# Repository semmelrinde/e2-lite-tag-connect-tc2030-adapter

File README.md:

# Renesas E2 emulator Lite → Tag-Connect TC2030 adapter (hand-solder, open hardware)

A small, hand-solderable KiCad adapter board that connects a **Renesas E2 emulator Lite** (20-pin 1.27 mm debug connector, RA family / SWD) to a **Tag-Connect TC2030-IDC** cable, so you can program and debug Renesas RA MCUs through a TC2030 footprint (for example RA8, RA6, RA4) without a header on your board.

| Top | Bottom |
|---|---|
|  |  |

*Renders from KiCad. The 3D model of J1 is a plain pin header; the real part is a shrouded box header.*

**Status (November 2026):** design finished and checked (ERC 0, DRC 0 errors / 0 warnings / 0 unconnected / schematic parity 0, two independent reviews of every connection). Not built yet. Reports from builders are welcome via Issues.

Deutsch: [Kurzfassung unten](#deutsch).

---

## What it does

```
E2 Lite ── 20-pin 1.27 mm ribbon cable ── J1 [adapter] J2 ── TC2030-IDC cable ── TC2030 footprint on your board
```

| J1 (E2 Lite, 20-pin) | Signal | On the adapter | J2 / TC2030 | Target |
|---|---|---|---|---|
| 1 | VCC (target voltage reference) | U1 ideal diode (target → emulator) | 1 | VTref |
| 2 | SWDIO | R1 100 Ω | 2 | SWDIO |
| 4 | SWCLK | R2 100 Ω | 4 | SWCLK |
| 10 | RES# | R3 100 Ω | 3 | nRESET |
| 3, 5, 9 (UCON), 15, 17, 19 | GND | direct | 5 | GND |
| 6, 7, 8, 11–14, 16, 18, 20 | – | not connected | 6 (SWO) not connected | – |

- The J1 pinout follows the Renesas document *E2 Emulator, E2 Emulator Lite Additional Document for User's Manual (Notes on Connection of RA Devices)*, R20UT4686, Table 2.3 (SWD). **Pin 9 (UCON) must be tied to GND**, otherwise the E2 Lite does not detect the target.
- The J2 pinout is the common TC2030 SWD layout: 1 VTref, 2 SWDIO, 3 nRESET, 4 SWCLK, 5 GND, 6 SWO. With the TC2030-IDC cable, pin n of the footprint goes to pin n of the 2×3 IDC plug.
- The E2 Lite has no SWO trace input (pin 6 is a UART TxD on the E2 Lite), so SWO stays open.

## Protection (and its limits)

- **U1 LM66100 ideal diode** (CE tied to VOUT, ST to GND, as in TI's "always-on reverse current blocking" application). The E2 Lite powers its I/O buffers from the VCC pin (about 20 mA). Your board's supply reaches the emulator through U1 with only a few mV drop.
- **What U1 blocks:** target board **off** and the emulator set to supply 3.3 V by mistake. U1 blocks, so 3.3 V does not reach your target's rail.
- **What U1 does not block reliably:** target board **on** and the emulator supplying 3.3 V at the same time. U1 only switches off at several hundred mA reverse current; the E2 Lite supplies at most 200 mA.
- **R1–R3 (100 Ω)** damp the cable and limit the current if 3.3 V levels ever reach a 1.8 V target. That limits damage, it does not prevent it.
- **Always set "Power Target From The Emulator" to No** in e² studio / Renesas Flash Programmer when the target has its own supply. The bottom silkscreen says so as well.
- The E2 Lite works from 1.8 V to 5.5 V target voltage. The adapter costs a few mV, so a target running at exactly 1.8 V is right at the lower limit.

## Bill of materials

| Ref | Qty | Part | Notes |
|---|---|---|---|
| J1 | 1 | 2×10 box header, 1.27 mm pitch, straight, through-hole, e.g. Samtec SHF-110-01-L-D-TH or a generic "DC3-20P 1.27 mm" | notch towards the board edge (odd-pin side), as on the silkscreen |
| J2 | 1 | 2×3 box header, 2.54 mm pitch, straight, through-hole, e.g. Würth 61200621621 or a generic "DC3-6P" | notch towards the middle of the board (odd-pin side), as on the silkscreen |
| U1 | 1 | TI LM66100DCKR (or the automotive LM66100QDCKRQ1, same pinout), SC-70-6 | footprint has extended pads for hand soldering |
| R1, R2, R3 | 3 | 100 Ω, 0603 | |
| C1, C2 | 2 | 100 nF, 0603, X7R | |
| C3 | 1 | 1 µF, 0603 | 470 nF … 2.2 µF also fine |

You also need:
- a **20-pin 1.27 mm IDC ribbon cable** (both plugs in the same orientation, pin 1 to pin 1). The Renesas cable RTE0T00020KCAC0000J fits for sure.
- a **Tag-Connect TC2030-IDC** (with legs) or **TC2030-IDC-NL** (no legs) cable from [Tag-Connect](https://www.tag-connect.com/product/tc2030-idc-6-pin-tag-connect-plug-of-nails-spring-pin-cable-with-legs).
- a **Renesas E2 emulator Lite** (RTE0T0002LKCE00000R), for example from DigiKey or Mouser.

### Where to get the small parts

**If you buy the E2 Lite from DigiKey anyway, get the small parts there too.** They add only a few francs, the order stays above the free-shipping threshold, and you get genuine parts. Prices and stock checked at DigiKey Switzerland on 4 November 2026 (without VAT, will change):

| Ref | Part number | Price | Notes |
|---|---|---|---|
| J1 | Samtec SHF-110-01-L-D-TH | CHF 2.25 | 19 mm long, about 0.4 mm longer than the outline on the board at the outer edge; harmless. Pins 0.41 mm square in 0.65 mm holes: a snug fit. |
| J2 | Würth 61200621621 | CHF 0.41 | |
| U1 | TI LM66100QDCKRQ1 (cut tape) | CHF 0.31 | LM66100DCKR was out of stock; the Q1 part is the automotive grade of the same chip |

#### AliExpress (checked November 2026)

Listings change, so every part also has a description and search words. The links are examples, not recommendations of a particular seller. Check the variant (pitch and pin count) before you pay.

| Part | Example listing | Choose this variant | Search words if the link is dead |
|---|---|---|---|
| J1 box header, 1.27 mm 2×10 | [item 1005006195593825](https://de.aliexpress.com/item/1005006195593825.html) | **1.27 mm, 20P**, straight (DIP) | `1.27mm box header 2x10 DC3 straight DIP` |
| J2 box header, 2.54 mm 2×3 | [item 1005007258589531](https://de.aliexpress.com/item/1005007258589531.html) (AliExpress Choice) or [item 1005006195593825](https://de.aliexpress.com/item/1005006195593825.html) | **6Pin** (10 pcs), straight (DIP) | `2.54mm box header 2x3 6P straight DC3` |
| U1 LM66100DCKR | [item 1005013241477993](https://de.aliexpress.com/item/1005013241477993.html) | 10 pcs, SC-70-6 | `LM66100DCKR SC70-6` |
| 20-pin 1.27 mm cable (alternative to the Renesas cable) | [item 1005006165132728](https://de.aliexpress.com/item/1005006165132728.html) | **pitch 1.27 mm**, 20P, same direction | `1.27mm IDC flat cable 20 pin 2x10 same direction` |
| 0603 resistor and capacitor kits | any 0603 kit with 100 Ω, 100 nF and 1 µF | | `0603 resistor kit`, `0603 capacitor kit 1pF-10uF` |

Shipping tip: on AliExpress every seller charges its own shipping, often more than the part itself. Choice items ship free once the Choice part of your order reaches the threshold (CHF 9 in Switzerland, November 2026).

Watch out: many "1.27 mm" ribbon cables have 2.54 mm plugs (the ribbon wires have a 1.27 mm pitch). For the E2 Lite you need **plugs with 1.27 mm pin pitch** (ribbon wire pitch 0.635 mm).

Pictures of the real parts: we do not copy seller photos (they belong to the sellers). The renders above show the footprints. Photos of an assembled board will be added once one is built.

## Ordering the PCB (JLCPCB or any other fab)

- Gerber files: [`fabrication/E2Lite_TC2030_Adapter_V1_gerbers.zip`](fabrication/E2Lite_TC2030_Adapter_V1_gerbers.zip)
- 2 layers, 26 × 19.5 mm, 1.6 mm FR-4, 1 oz copper, any colour, HASL (lead-free) or ENIG, tented vias, standard via size 0.3 mm (0.6 mm pad). No special options needed.

### Save money: add it to a PCB order you already have

If you work with Tag-Connect, you almost certainly have your own PCB in production anyway. Add the adapter as an extra design to that order (at JLCPCB: "Add new item" on the running order, or put both in the same cart). Everything then ships in one parcel.

Example from a JLCPCB quote on 4 November 2026 (5 pcs, shipping to Switzerland, prices in EUR, will change):

| | Board (5 pcs) | Shipping | Total |
|---|---|---|---|
| Ordered on its own | €3.66 (green HASL) … €4.64 (black, lead-free HASL) | €20.92 (DHL Express, 0.14 kg) | **€24.58 … €25.56** |
| Added to an order that ships anyway | €3.66 … €4.64 | about €0 (adds roughly 10 g) | **€3.66 … €4.64** |
| **You save** | | | **about €21 (≈ 82–85 %)** |

Shipping cost depends on your country, the carrier and the weight of the whole parcel. With JLCPCB the combined order only ships when every item in it is finished.

## Assembly (hand soldering)

1. **U1 first:** a little solder paste or flux, pin 1 (dot) at the silkscreen triangle. The pads are extended for a soldering iron.
2. **C1–C3, R1–R3** (0603, large pads).
3. **J1:** insert from the top, **notch on the outer edge (odd-pin side)** as on the silkscreen. The pins are 1.27 mm apart: use a fine tip and remove bridges with wick.
4. **J2:** notch towards the middle of the board, as on the silkscreen.
5. If U1 does not work (for example a bad part): remove it and bridge **pad 1 to pad 6** (same row, about 2 mm apart). VCC is then connected directly, as in Renesas' reference circuit, without the reverse-current protection.

## Check before first use (adapter alone, no target)

| From J1 | To J2 | Expected |
|---|---|---|
| 2 | 2 | ≈ 100 Ω |
| 4 | 4 | ≈ 100 Ω |
| 10 | 3 | ≈ 100 Ω |
| 3, 5, 9, 15, 17, 19 | 5 | 0 Ω |
| 1 | 1 | no short; diode test + at J2.1, − at J1.1: about 0.4–0.7 V (U1 body diode, estimate), reverse open |
| 1 vs 3 | 1 vs 5 | no short to GND |
| 6, 7, 8, 11–14, 16, 18, 20 | – | open |

Check the ribbon cable too: pin 1 must reach pin 1 at both ends (red wire).

### Power-up order (from the Renesas user manual)

1. Target off.
2. Connect adapter and cables.
3. Plug the E2 Lite into USB.
4. Start the debugger or flash tool, set "Power Target From The Emulator: No".
5. Switch the target on.
6. Connect in the software.

Reverse order when you finish. Do not unplug the E2 Lite's USB cable while the target is powered (Renesas warns about leakage currents).

## Files

```
hardware/      KiCad 10 project (schematic, PCB, footprints, 3D models from the KiCad library)
hardware/gen/  Python scripts that generate the schematic and the PCB (optional; macOS KiCad paths)
fabrication/   Gerber + drill files (zip)
images/        3D renders, schematic (PDF, SVG)
```

Custom footprints: `BoxHeader_2x10_P1.27mm_Vertical_DC3` (pins as KiCad `PinHeader_2x10_P1.27mm_Vertical`, drill 0.65 mm, assumed body 5.8 × 16.2 mm) and `SOT-363_SC-70-6_HandSolder` (KiCad pad positions, pads extended outwards).

## Related

- [ST-LINK V3 / ARM 20-pin → Tag-Connect TC2030 adapter](https://github.com/semmelrinde/stlink-v3-tag-connect-tc2030-adapter)

## Licence and disclaimer

- Hardware design, documentation and scripts: **CERN-OHL-P-2.0** ([LICENSE](LICENSE)). You may use, modify, make and sell it. The design comes without any warranty, see the licence.
- Footprints and 3D models taken from the KiCad libraries: CC-BY-SA 4.0 with the KiCad library exception, see [NOTICE.md](NOTICE.md).
- **Not affiliated with or endorsed by** Renesas Electronics, Tag-Connect LLC, Texas Instruments, Samtec, Würth Elektronik, DigiKey, AliExpress or any other manufacturer or shop. Product names and trademarks belong to their owners and are used only to describe compatibility. No manufacturer datasheets, manual text or seller photos are included; please get them from the original sources.
- You use this adapter at your own risk. Check pinouts against your own board and debugger before connecting anything.

---

## Deutsch

Kleiner Adapter zum Selberlöten: **Renesas E2 emulator Lite** (20-polig, 1,27 mm) auf **Tag-Connect TC2030-IDC**. Damit programmierst und debuggst du Renesas-RA-Mikrocontroller über ein TC2030-Pad.

- **Belegung:** wie in der Tabelle oben. Pin 9 (UCON) liegt auf Masse.
- **Schutz:** Die Idealdiode LM66100 schützt nur bei ausgeschaltetem Zielboard vor den 3,3 V des Emulators. Darum im Programm immer „Power Target From The Emulator: No“ einstellen.
- **Teile:** zwei Wannenstecker (1,27 mm 2×10 und 2,54 mm 2×3), LM66100, drei 100-Ω-Widerstände, zwei 100-nF- und ein 1-µF-Kondensator, alle 0603. Links und Suchbegriffe stehen in der Tabelle. Wer den E2 Lite bei DigiKey kauft, nimmt die Kleinteile dort mit (Samtec SHF-110-01-L-D-TH, Würth 61200621621, LM66100QDCKRQ1): kein eigener Versand, Originalteile.
- **Sparen:** Die Platine zu einer Leiterplattenbestellung dazulegen, die du sowieso hast. Dann fällt der eigene Versand weg, bei JLCPCB am 4.11.2026 etwa €21.
- Lizenz: CERN-OHL-P-2.0. Ohne Gewähr. Keine Verbindung zu Renesas oder Tag-Connect.

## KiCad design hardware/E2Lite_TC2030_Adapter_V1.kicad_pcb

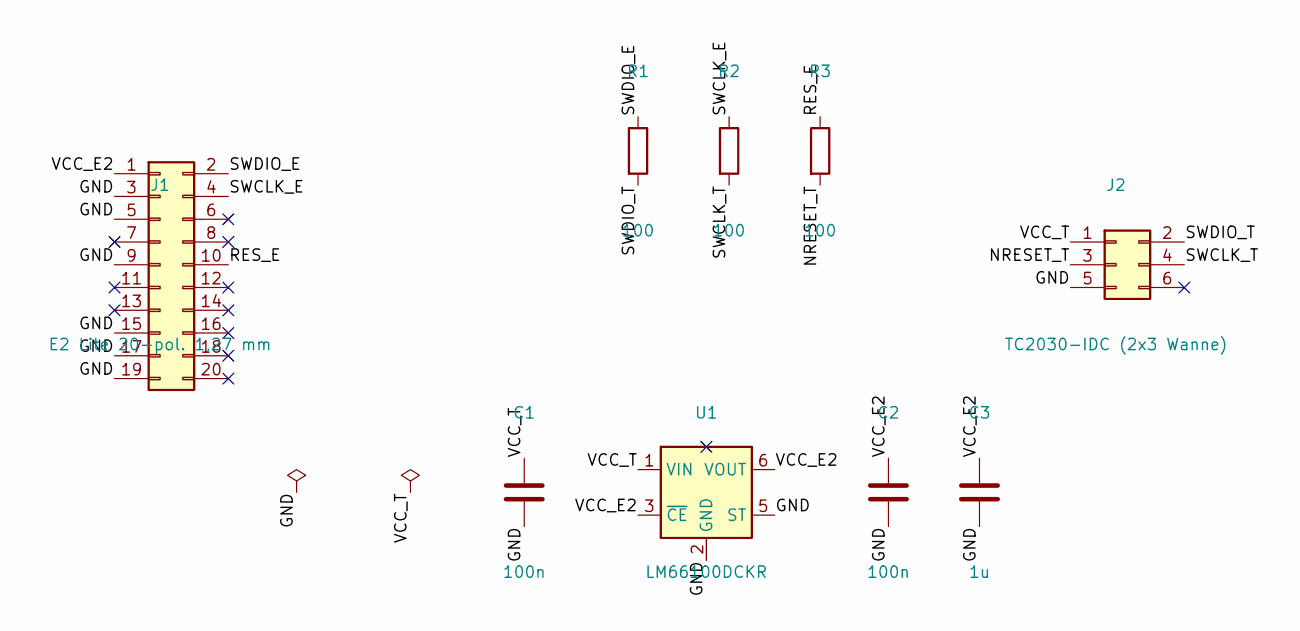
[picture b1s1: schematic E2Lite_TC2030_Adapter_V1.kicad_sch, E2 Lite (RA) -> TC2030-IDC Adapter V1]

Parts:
C1, C2: 100n; C_0603_1608Metric_Pad1.08x0.95mm_HandSolder; MPN 100 nF 0603
C3: 1u; C_0603_1608Metric_Pad1.08x0.95mm_HandSolder; MPN 1 uF 0603
J1: E2 Lite 20-pol. 1,27 mm; BoxHeader_2x10_P1.27mm_Vertical_DC3; MPN DC3 Wannenstecker 2x10 1,27 mm gerade T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
J2: TC2030-IDC (2x3 Wanne); IDC-Header_2x03_P2.54mm_Vertical; MPN Wannenstecker 2x3 2,54 mm gerade THT
R1, R2, R3: 100; R_0603_1608Metric_Pad0.98x0.95mm_HandSolder; MPN 100 Ohm 0603
U1: LM66100DCKR; SOT-363_SC-70-6_HandSolder; MPN LM66100DCKR

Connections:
/GND: C1.2, C2.2, C3.2, J1.3, J1.5, J1.9, J1.15, J1.17, J1.19, J2.5, U1.2 (GND), U1.5 (ST)
/NRESET_T: J2.3, R3.2
/RES_E: J1.10, R3.1
/SWCLK_E: J1.4, R2.1
/SWCLK_T: J2.4, R2.2
/SWDIO_E: J1.2, R1.1
/SWDIO_T: J2.2, R1.2
/VCC_E2: C2.1, C3.1, J1.1, U1.3 (~CE), U1.6 (VOUT)
/VCC_T: C1.1, J2.1, U1.1 (VIN)

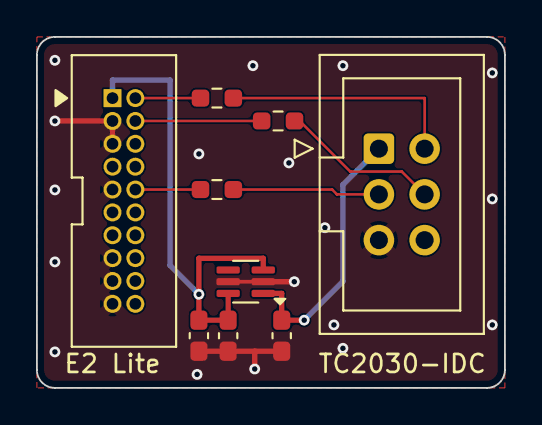
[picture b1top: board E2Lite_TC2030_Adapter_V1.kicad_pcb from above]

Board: 2 copper layers, 26.0 x 19.5 mm, 9 parts (0 on the bottom side), 9 nets.

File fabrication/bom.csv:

Reference,Qty,Value,Package,Description,Example part
J1,1,2x10 box header 1.27 mm,THT straight,E2 Lite 20-pin connector (notch on odd-pin side),DC3-20P 1.27 mm box header
J2,1,2x3 box header 2.54 mm,THT straight,TC2030-IDC connector (notch on odd-pin side),DC3-6P 2.54 mm box header
U1,1,LM66100DCKR,SC-70-6,Ideal diode (CE=VOUT, ST=GND),Texas Instruments LM66100DCKR
R1 R2 R3,3,100 Ohm,0603,Series resistors SWDIO/SWCLK/RES#,any 0603 1% or 5%
C1 C2,2,100 nF,0603,Decoupling,X7R 16 V or more
C3,1,1 uF,0603,Decoupling E2 Lite I/O supply,X5R/X7R 10 V or more
